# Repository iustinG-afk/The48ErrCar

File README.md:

# The48ErrCar: ESP32-S3 RC Car Controller Board

A custom-designed PCB that turns an RC car chassis into a Wi-Fi-controlled, sensor-equipped vehicle, driven from a mobile app built in MIT App Inventor.

I designed the board from scratch in KiCad, wrote the firmware in C (ESP-IDF) with the help of AI, hand-soldered every component, and built the control app. This was my first PCB project, so this repository also documents what went wrong and what I learned from it.

---

## Highlights

- **Custom 2-layer PCB** designed in KiCad, with an ESP32-S3-WROOM-1 at its core
- **Two buck converters** from a 7.4 V battery pack (2x 18650 in series): one to 3.3 V for logic, one to 5 V for peripherals
- **Dual-motor-pair drive** through a DRV8833 H-bridge, plus servo steering
- **Wi-Fi control**: the ESP32 hosts its own access point and a small web server, and the phone app talks to it over HTTP
- **Native USB-C programming** through the ESP32-S3's built-in USB controller, so no USB-to-serial chip is needed
- **Hand-assembled** with a soldering iron and heat gun (SMD, 0805/1206 passives, SOIC and HTSSOP packages)

---

## Features

| Feature | Status | Notes |
|---|---|---|
| Forward / reverse drive | Working | PWM speed control through DRV8833 |
| Steering | Working | Servo driven by PWM |
| Front headlights | Working | N-MOS low-side switching |
| Brake / rear lights | Working | Automatically on when reversing or braking, with a manual override |
| Left / right turn signals | Working | Blinking at 500 ms |
| Horn / buzzer | Working | Hold-to-sound from the app |
| Water pump | Working | Low-side N-MOS switch with flyback diode |
| Temperature & humidity (DHT11) | Working | Read on demand from the app |
| Ultrasonic rear parking sensor | Working | Cuts reverse motor power at 5 cm or closer and beeps |
| Clap-controlled turn signals | Working, limited | Microphone detects volume spikes: 2 claps = left, 3 claps = right, 4 claps = hazard |
| Camera (OV3660, 24-pin FPC) | **Not working** | See [Known issues](#known-issues) |

---

## System overview

```
                    2x 18650 (≅7.4 V)
                           |
                   [3A PTC polyfuse]
                           |
          +----------------+----------------+
          |                |                |
   Buck -> 3.3 V     Buck -> 5 V        Motor supply
   (TPS54331)        (TPS54331)           (7.4 V)
          |                |                |
   ESP32-S3, DHT11,   Servo, pump,       DRV8833
   mic, camera LDO    buzzer, US sensor   -> L / R motor pairs
          |
   ESP32-S3 (Wi-Fi AP + HTTP server)
          ^
          | HTTP over Wi-Fi
          |
   MIT App Inventor app (phone)
```

---

## Hardware

### Power

- **Battery:** 7.4 V (2x Li-Ion 18650 in series), protected by a **3 A resettable PTC polyfuse**.
- **3.3 V rail:** TPS54331 buck converter, 10 µH inductor, 22 µF output capacitor. Feedback divider 31.6 kΩ / 10 kΩ gives about 3.33 V. Soft-start, bootstrap and compensation networks are included.
- **5 V rail:** a second TPS54331 stage (52.3 kΩ / 10 kΩ divider) for the servo, pump, buzzer and ultrasonic sensor.
- **Why buck converters instead of linear regulators:** they step the voltage down by fast switching rather than burning the difference as heat, which matters when running from a battery.
- **Test points** on +7.4 V, +5 V, +3.3 V and GND for easy debugging.

### Microcontroller

- **ESP32-S3-WROOM-1** (integrated antenna and matching network)
- Reset/boot circuitry: RC delay on `EN`, pull-ups, and two buttons for reset and download mode
- Local decoupling (22 µF + 100 nF) placed directly beside the module
- USB-C connector wired straight to the S3's native USB D+/D- (CC pull-downs of 5.1 kΩ)

### Motor driver and steering

- **DRV8833** dual H-bridge drives the left-side and right-side motor pairs (connectors J5 / J4)
- Bulk capacitor on the motor supply to absorb current spikes when starting or stalling
- Current-sense pins tied to ground (full current)
- Servo signal on a 3-pin header

### Switched loads

Water pump, buzzer and four lights (front, rear, left and right signals) each use a **logic-level N-MOSFET low-side switch** with:

- a **10 kΩ pull-down** on every gate, so nothing switches on randomly while the ESP32 is booting
- a **Schottky flyback diode** on inductive loads (pump, buzzer)
- **220 Ω** current-limiting resistors on the LEDs

### Connectors

Sensors, motors, servo, microphone and lights connect through **pin headers and jumper wires** rather than being soldered to the board, so they can be mounted wherever they fit on the chassis.

| PCB layout | 3D render |
|---|---|
|  |  |

---

## Firmware

Written in C with **ESP-IDF** and **FreeRTOS** (`main.c`).

- Starts a **Wi-Fi access point** and an **HTTP server** on the ESP32 (default address `192.168.4.1`)
- Control endpoint `/cmd?c=...` handles lights, signals, horn, pump, microphone mode and drive commands; `/dht` returns temperature and humidity
- Drive and steering use **LEDC PWM** channels
- Dedicated FreeRTOS tasks run in parallel for:
  - **turn signals / rear lights**
  - **reverse safety**, using an ultrasonic distance check that stops the motors at 5 cm or closer
  - **clap detection**, sampling the microphone through the ADC and counting volume spikes
- DHT11 is read with a custom bit-banged driver
- MJPEG camera stream server on `/stream` (disabled in practice because the camera hardware does not work, see below)

> **Security note:** the access point name and password are defined in `main.c`. Change them before using the car anywhere other than your desk.

---

## Mobile app

Built in **MIT App Inventor** (block-based). The app:

- shows an intro screen and checks the connection by pinging the car (`/cmd?c=ping`)
- enables the **Start** button only once the car answers, and shows "Connect to Wi-Fi!" if it times out
- provides the control interface for driving, lights, signals, horn, pump, temperature and microphone mode
- includes a credits screen with links to my Instagram, LinkedIn and GitHub

| Start | Credits |
|---|---|
|  |  |

The App Inventor block screenshots are in [`MIT/`](MIT).

---

## Design revisions

**V1 (fabricated and assembled)**
- Built and soldered by hand. Most of the board works, but it has the issues described below.

**V2 (current layout in this repository)**
- Corrected the MOSFET footprints (the V1 pinout was wrong, see below)
- Added a **1.5 V LDO (AMS1117-1.5)** with 2x 10 µF capacitors for the camera supply
- Added **4.7 kΩ I²C pull-ups** on the camera SDA/SCL lines
- Reworked routing around the camera connector

**V3 (through-hole version)**
- A through-hole variant of the board for easier hand assembly, built after the SMD experience

| Schematic | PCB layout | 3D render |
|---|---|---|
| |  |  |

---

## Known issues

This was my first PCB, and I would rather document the mistakes honestly than hide them:

1. **MOSFET pinout reversed.** I used an N-MOS symbol and footprint with a gate-source-drain order that doesn't match the actual SOT-23 parts. On the fabricated V1 board, the six transistors had to be fitted **upside down on the back of the board** to work. Fixed in V2.
2. **Camera does not work.** I designed for an OV2640, but the module I received from AliExpress turned out to be an OV3660. The pinout is very similar, so the firmware targets the OV3660. I didn't realise the 24-pin FPC connector is numbered 1 to 24 and wired my pin mapping in reverse. I tried a reversing workaround, but the camera never came up. The cause may also be a damaged connector or poor pad contact after rework. I also initially forgot the 1.5 V supply that the camera needs, which V2 adds.
3. **Microphone is a spike detector, not an audio input.** It only measures volume peaks, which is enough for clap detection but not for recording sound.
4. **Layout is not optimal.** The routing was rushed. The V2 layout cleans it up, but it has not been fabricated.

---

## What I learned

- Always check pin numbering and orientation against the datasheet and footprint, and verify symbol pin order, not just names
- Add pull-down resistors on MOSFET gates and understand why
- How buck converters work: feedback dividers, soft-start, bootstrap, compensation, inductor and diode placement
- The value of decoupling capacitors and keeping switching components away from the antenna
- Hand-soldering SMD parts with an iron and heat gun is hard, and rewarding
- Firmware design on ESP-IDF with FreeRTOS tasks

---

## Bill of materials (summary)

| Qty | Part |
|---|---|
| 1 | ESP32-S3-WROOM-1 |
| 2 | TPS54331D buck converter (SOIC-8) |
| 1 | DRV8833PWP motor driver (HTSSOP-16) |
| 1 | AMS1117-1.5 LDO (V2) |
| 6 | N-channel MOSFET (SOT-23) |
| 4 | Schottky diode (SMA) |
| 2 | 10 µH inductor |
| 1 | 3 A PTC resettable fuse |
| 1 | USB-C receptacle |
| 1 | 24-pin 0.5 mm FPC connector |
| 22 | 0805 resistors |
| 9 / 7 | 0805 / 1206 capacitors |
| 2 | Tactile push buttons |
| 1 | Buzzer |
| - | Pin headers |

Off-board: DC motors, servo, DHT11, HC-SR04-style ultrasonic sensor, microphone module, water pump, LEDs, 2x 18650 cells.

---

## Repository structure

```
.
|-- docs/      images, gifs, documentation
|-- Through-hole/     KiCad project, schematic, layout V2
|-- MIT/           MIT App Inventor project pictures, videos, logo
|-- The48ErrCar.apk      Apk to download the app
|-- firmware.c/          ESP-32 Code
|-- hardware.c/          KiCad project, schematic, layout

```

## Assembly

The board was assembled entirely by hand with a soldering iron and a heat gun.

## Status

The board, firmware and app work together. The car was **not assembled onto a chassis**: my focus was the PCB design, schematic and firmware, so mounting is left as a DIY step.

## Author

**Iustin George**: [GitHub](https://github.com/iustinG-afk) · [LinkedIn](www.linkedin.com/in/vrînceanu-george-iustin-437aa3331) · [Instagram](https://www.instagram.com/iustin_george10/)

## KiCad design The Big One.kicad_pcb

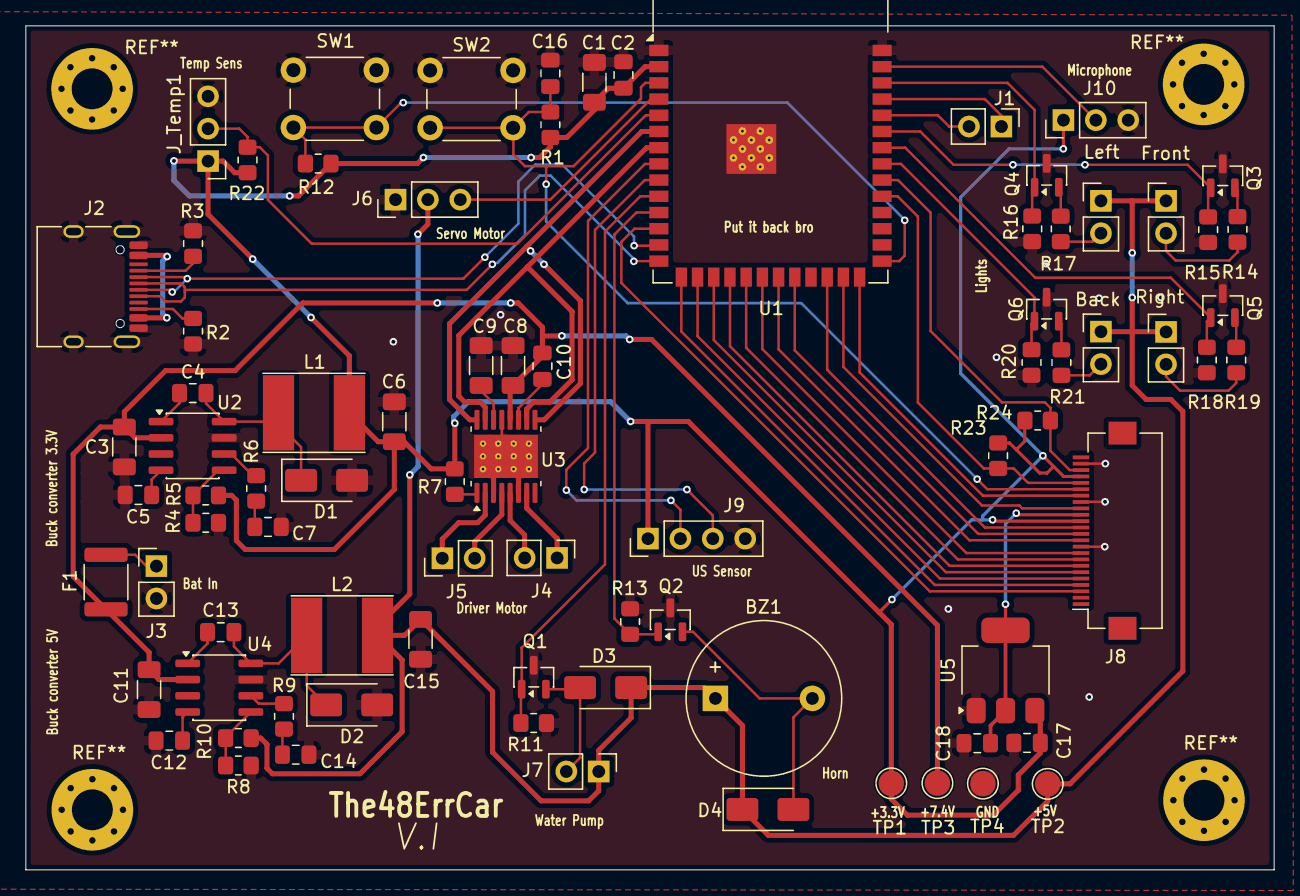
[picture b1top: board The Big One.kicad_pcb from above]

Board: 2 copper layers, 97.8 x 66.2 mm, 82 parts (0 on the bottom side), 71 nets.

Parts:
BZ1: Buzzer; Buzzer_12x9.5RM7.6
Back: Conn_01x02; PinHeader_1x02_P2.54mm_Vertical
C1, C6, C15: 22u; C_1206_3216Metric_Pad1.33x1.80mm_HandSolder
C2, C4, C13: 100n; C_0805_2012Metric_Pad1.18x1.45mm_HandSolder
C3, C8, C11: 10u; C_1206_3216Metric_Pad1.33x1.80mm_HandSolder
C5, C12: 47n; C_0805_2012Metric_Pad1.18x1.45mm_HandSolder
C7, C14: 2.2n; C_0805_2012Metric_Pad1.18x1.45mm_HandSolder
C9: 2.2u; C_1206_3216Metric_Pad1.33x1.80mm_HandSolder
C10: 10n; C_0805_2012Metric_Pad1.18x1.45mm_HandSolder
C16: 1u; C_0805_2012Metric_Pad1.18x1.45mm_HandSolder
C17, C18: 10uF; C_0805_2012Metric_Pad1.18x1.45mm_HandSolder
D1, D2, D3, D4: D_Schottky; D_SMA
F1: 3A; Fuse_1812_4532Metric
Front: Conn_01x02; PinHeader_1x02_P2.54mm_Vertical
J1, J3, J4, J5, J7: Conn_01x02; PinHeader_1x02_P2.54mm_Vertical
J2: USB_C_Receptacle_USB2.0_16P; USB_C_Receptacle_HRO_TYPE-C-31-M-12
J6, J10: Conn_01x03; PinHeader_1x03_P2.54mm_Vertical
J8: Conn_01x24; Hirose_FH12-24S-0.5SH_1x24-1MP_P0.50mm_Horizontal
J9: Conn_01x04; PinHeader_1x04_P2.54mm_Vertical
J_Temp1: Conn_01x03; PinHeader_1x03_P2.54mm_Vertical
L1, L2: 10u; L_Taiyo-Yuden_NR-60xx_HandSoldering
Left: Conn_01x02; PinHeader_1x02_P2.54mm_Vertical
Q1, Q2, Q3, Q4, Q5, Q6: Q_NMOS_GDS; SOT-23
R1, R4, R7, R8, R11, R12, R13, R15, R16, R18, R20, R22: 10k; R_0805_2012Metric_Pad1.20x1.40mm_HandSolder
R2, R3: 5.1k; R_0805_2012Metric_Pad1.20x1.40mm_HandSolder
R5: 31.6k; R_0805_2012Metric_Pad1.20x1.40mm_HandSolder
R6, R9: 22k; R_0805_2012Metric_Pad1.20x1.40mm_HandSolder
R10: 52.3k; R_0805_2012Metric_Pad1.20x1.40mm_HandSolder
R14, R17, R19, R21: 220; R_0805_2012Metric_Pad1.20x1.40mm_HandSolder
R23, R24: 4.7k; R_0805_2012Metric_Pad1.20x1.40mm_HandSolder
Right: Conn_01x02; PinHeader_1x02_P2.54mm_Vertical
SW1, SW2: SW_Push; SW_PUSH_6mm_H5mm
TP1, TP2, TP3, TP4: TestPoint; TestPoint_Pad_D2.0mm
U1: ESP32-S3-WROOM-1
U2, U4: TPS54331D; SOIC-8_3.9x4.9mm_P1.27mm
U3: DRV8833PWP; HTSSOP-16-1EP_4.4x5mm_P0.65mm_EP3.4x5mm_Mask2.46x2.31mm_The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
U5: AMS1117-1.5; SOT-223-3_TabPin2

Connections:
+3.3V: C1.2, C2.1, C6.1, C17.1, J8.14, J8.21, J9.1, J10.1, J_Temp1.1, L1.2, R1.2, R5.2, R7.2, R12.2, R22.1, R23.1, R24.1, TP1.1 (1_1), U1.2 (3V3), U5.3 (VI)
+5V: BZ1.1 (+), Back.1, C15.1, D3.1 (K), D4.1 (K), Front.1, J6.2, J7.1, L2.2, Left.1, R10.2, Right.1, TP2.1 (1_1)
+7.4V: C3.2, C8.1, C10.1, C11.2, F1.2, TP3.1 (1_1), U2.2 (VIN), U3.12 (VM), U4.2 (VIN)
/1.5V: C18.1, J8.15, U5.2 (VO)
/+5V_USB: J2.A4 (VBUS), J2.A9 (VBUS), J2.B4 (VBUS), J2.B9 (VBUS)
/Cam_D0: J8.6, U1.17 (IO9)
/Cam_D1: J8.4, U1.15 (IO3)
/Cam_D2: J8.3, U1.12 (IO8)
/Cam_D3: J8.5, U1.16 (IO46)
/Cam_D4: J8.7, U1.18 (IO10)
/Cam_D5: J8.9, U1.20 (IO12)
/Cam_D6: J8.11, U1.21 (IO13)
/Cam_D7: J8.13, U1.24 (IO47)
/Cam_HREF: J8.16, U1.25 (IO48)
/Cam_PCLK: J8.8, U1.19 (IO11)
/Cam_SCL: J8.20, R23.2, U1.31 (IO38)
/Cam_SDA: J8.22, R24.2, U1.32 (IO39)
/Cam_VSYNC: J8.18, U1.26 (IO45)
/Cam_XCLK: J8.12, U1.22 (IO14)
/D+: J2.A6 (D+), J2.B6 (D+), U1.14 (USB_D+)
/D-: J2.A7 (D-), J2.B7 (D-), U1.13 (USB_D-)
/EN: C16.2, J8.19, R1.1, SW2.2, U1.3 (EN)
/Horn_CTRL: Q2.1 (G), R13.2, U1.11 (IO18)
/Light_Back: Q6.1 (G), R20.1, U1.33 (IO40)
/Light_Front: Q3.1 (G), R15.1, U1.35 (IO42)
/Light_Turn_L: Q4.1 (G), R16.1, U1.38 (IO2)
/Light_Turn_R: Q5.1 (G), R18.1, U1.34 (IO41)
/MIC_OUT: J10.2, U1.39 (IO1)
/Motor_FWD: U1.6 (IO6), U3.9 (BIN1), U3.16 (AIN1)
/Motor_REV: U1.7 (IO7), U3.10 (BIN2), U3.15 (AIN2)
/Pump_CTRL: Q1.1 (G), R11.1, U1.10 (IO17)
/Servo_PWM: J6.3, U1.4 (IO4)
/Temp_Data: J_Temp1.2, R22.2, U1.5 (IO5)
/US_ECHO: J9.3, U1.9 (IO16)
/US_TRIG: J9.2, U1.8 (IO15)
/Vs_3.3: R4.1, R5.1, U2.5 (VSENSE)
/Vs_5: R8.1, R10.1, U4.5 (VSENSE)
GND: C1.1, C2.2, C3.1, C5.1, C6.2, C7.2, C8.2, C9.1, C11.1, C12.1, C14.2, C15.2, C16.1, C17.2, C18.2, D1.2 (A), D2.2 (A), J2.A1 (GND), J2.A12 (GND), J2.B1 (GND), J2.B12 (GND), J2.SH (SHIELD), J3.2, J6.1, J8.10, J8.17, J8.23, J9.4, J10.3, J_Temp1.3, Q1.3 (S), Q2.3 (S), Q3.3 (S), Q4.3 (S), Q5.3 (S), Q6.3 (S), R2.1, R3.1, R4.2, R8.2, R11.2, R13.1, R15.2, R16.2, R18.2, R20.2, SW1.1, SW2.1, TP4.1 (1_1), U1.1 (GND), U1.40 (GND), U1.41 (GND), U2.7 (GND), U3.3 (AISEN), U3.6 (BISEN), U3.13 (GND), U3.17 (GND), U4.7 (GND), U5.1 (GND)
unnamed: BZ1.2 (-), D4.2 (A), Q2.2 (D)
unnamed: C7.1, R6.2
unnamed: C14.1, R9.2
unnamed: C4.1, D1.1 (K), L1.1, U2.8 (PH)
unnamed: C13.1, D2.1 (K), L2.1, U4.8 (PH)
unnamed: D3.2 (A), J7.2, Q1.2 (D)
unnamed: J1.1, U1.37 (TXD0)
unnamed: J1.2, U1.36 (RXD0)
unnamed: J2.A5 (CC1), R3.2
unnamed: J2.B5 (CC2), R2.2
unnamed: F1.1, J3.1
unnamed: J4.1, U3.7 (BOUT1)
unnamed: J4.2, U3.5 (BOUT2)
unnamed: J5.1, U3.2 (AOUT1)
unnamed: J5.2, U3.4 (AOUT2)
unnamed: Back.2, R21.1
unnamed: Front.2, R14.1
unnamed: Left.2, R17.1
unnamed: R19.1, Right.2
unnamed: Q3.2 (D), R14.2
unnamed: Q4.2 (D), R17.2
unnamed: Q5.2 (D), R19.2
unnamed: Q6.2 (D), R21.2
unnamed: R12.1, SW1.2, U1.27 (IO0)
unnamed: C4.2, U2.1 (BOOT)
unnamed: R6.1, U2.6 (COMP)
unnamed: C5.2, U2.4 (SS)
unnamed: C10.2, U3.11 (VCP)
unnamed: C9.2, U3.14 (VINT)
unnamed: R7.1, U3.1 (~SLEEP)
unnamed: C13.2, U4.1 (BOOT)
unnamed: R9.1, U4.6 (COMP)
unnamed: C12.2, U4.4 (SS)

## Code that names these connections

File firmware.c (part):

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// PIN CONNECTIONS
#define PIN_SERVO      4    // IO4
#define PIN_DHT        5    // IO5
#define PIN_MOTOR_FWD  6    // IO6
#define PIN_MOTOR_REV  7    // IO7
#define PIN_US_TRIG    15   // IO15
#define PIN_US_ECHO    16   // IO16
#define PIN_PUMP      17   // IO17
#define PIN_BUZZER     18   // IO18
#define PIN_BACKLIGHTS      40   // IO40
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// ULTRASONIC SENSOR
// HC-SR04 style: 10us trigger pulse, then the echo pulse width is proportional to distance
float distance_cm() {
    gpio_set_level(PIN_US_TRIG, 0);
    esp_rom_delay_us(2);
    gpio_set_level(PIN_US_TRIG, 1);
    esp_rom_delay_us(10);
    gpio_set_level(PIN_US_TRIG, 0);

    // Wait for echo to go high; 30ms timeout means nothing was detected
    int64_t start_time = esp_timer_get_time();
    while (gpio_get_level(PIN_US_ECHO) == 0) {
        if ((esp_timer_get_time() - start_time) > 30000) return 999.0f; 
    }

    int64_t pulse_start = esp_timer_get_time();
    while (gpio_get_level(PIN_US_ECHO) == 1) {
        if ((esp_timer_get_time() - pulse_start) > 30000) break;
    }
    int64_t pulse_end = esp_timer_get_time();
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    gpio_set_level(PIN_BUZZER, BUZZER_MUTE); 

    // Simple on/off outputs, all start LOW
    int out_pins[] = {PIN_HEADLIGHTS, PIN_BACKLIGHTS, PIN_SIGNAL_L, PIN_SIGNAL_R, PIN_PUMP, PIN_US_TRIG};
    for(int i = 0; i < 6; i++) {
        gpio_reset_pin(out_pins[i]);
        gpio_set_direction(out_pins[i], GPIO_MODE_OUTPUT);
        gpio_set_level(out_pins[i], 0);
    }
    
    gpio_reset_pin(PIN_US_ECHO);
    gpio_set_direction(PIN_US_ECHO, GPIO_MODE_INPUT);

    // Servo: 50Hz (20ms period), 13-bit resolution = 8192 steps.
    // Duty 614 is ~1.5ms = centered; the UI sweeps 614 +/- 180.
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        .channel        = LEDC_CHANNEL_1,
        .timer_sel      = LEDC_TIMER_1,
        .intr_type      = LEDC_INTR_DISABLE,
        .gpio_num       = PIN_MOTOR_FWD,
        .duty           = 0, 
        .hpoint         = 0
    };
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        .channel        = LEDC_CHANNEL_2,
        .timer_sel      = LEDC_TIMER_1,
        .intr_type      = LEDC_INTR_DISABLE,
        .gpio_num       = PIN_MOTOR_REV,
        .duty           = 0, 
        .hpoint         = 0
    };
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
